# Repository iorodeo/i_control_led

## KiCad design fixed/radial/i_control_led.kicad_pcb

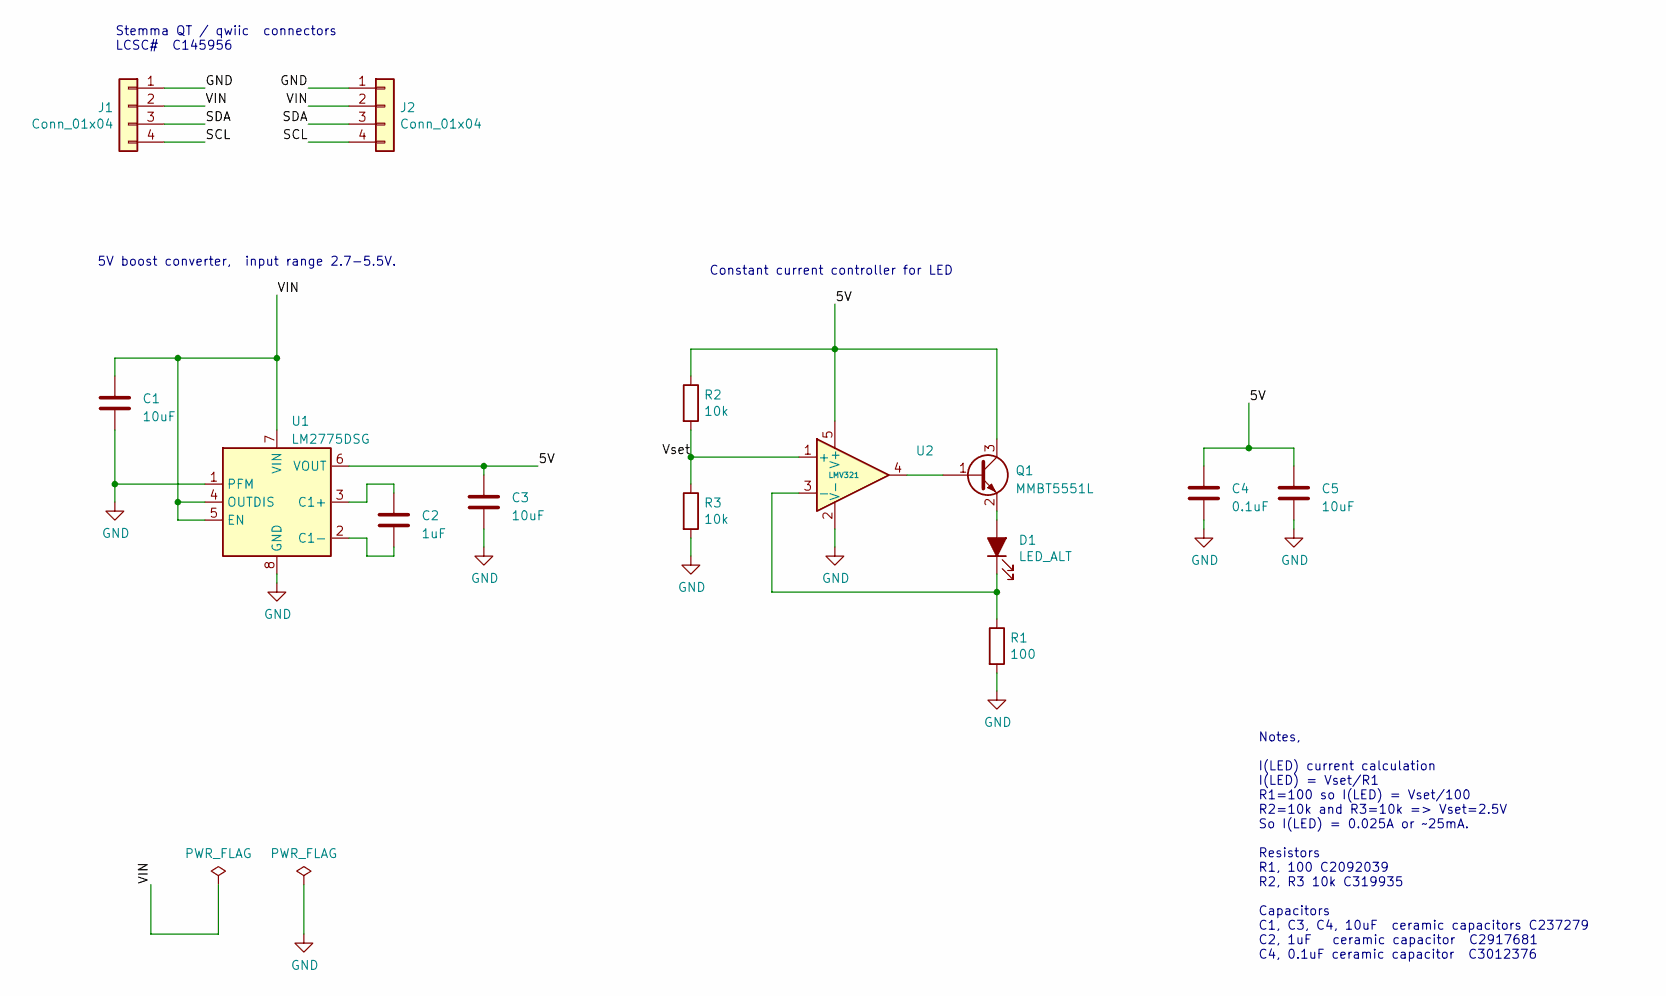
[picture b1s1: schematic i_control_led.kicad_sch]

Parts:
C1, C3, C5: 10uF; C_0402_1005Metric
C2: 1uF; C_0402_1005Metric
C4: 0.1uF; C_0402_1005Metric
D1: LED_ALT; LED_D3.0mm
J1, J2: Conn_01x04; BOOMELE_SMD_SH_4PIN_RT
Q1: MMBT5551L; SOT-23
R1: 100; R_0402_1005Metric
R2, R3: 10k; R_0402_1005Metric
U1: LM2775DSG; WSON-8-1EP_2x2mm_P0.5mm_EP0.9x1.6mm_ThermalVias
U2: LMV321; SOT-23-5

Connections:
/5V: C3.1, C4.1, C5.1, Q1.3 (C), R2.1, U1.6 (VOUT), U2.5 (V+)
/SCL: J1.4, J2.4
/SDA: J1.3, J2.3
/VIN: C1.2, J1.2, J2.2, U1.4 (OUTDIS), U1.5 (EN), U1.7 (VIN)
/Vset: R2.2, R3.1, U2.1 (+)
GND: C1.1, C3.2, C4.2, C5.2, J1.1, J2.1, R1.2, R3.2, U1.1 (PFM), U1.8 (GND), U1.9 (GND), U2.2 (V-)
unnamed: D1.2 (A), Q1.2 (E)
unnamed: D1.1 (K), R1.1, U2.3 (-)
unnamed: Q1.1 (B), U2.4
unnamed: C2.1, U1.3 (C1+)
unnamed: C2.2, U1.2 (C1-)

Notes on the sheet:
Stemma QT / qwiic connectors LCSC# C145956
Constant current controller for LED
Notes, I(LED) current calculation I(LED) = Vset/R1 R1=100 so I(LED) = Vset/100 R2=10k and R3=10k => Vset=2.5V So I(LED) = 0.025A or ~25mA. Resistors R1, 100 C2092039 R2, R3 10k C319935 Capacitors C1, C3, C4, 10uF ceramic capacitors C237279 C2, 1uF ceramic capacitor C2917681 C4, 0.1uF ceramic capaci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
5V boost converter, input range 2.7-5.5V.

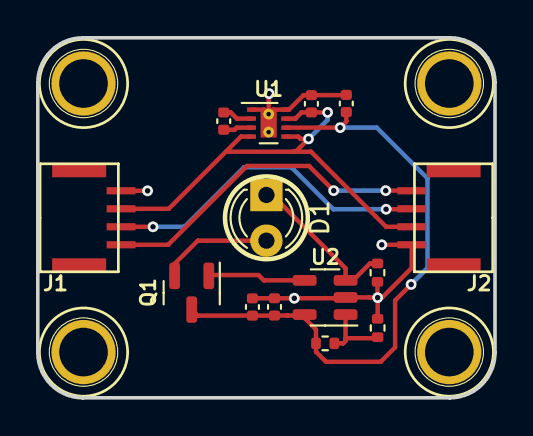
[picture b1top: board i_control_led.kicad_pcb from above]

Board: 2 copper layers, 25.4 x 20.0 mm, 18 parts (0 on the bottom side), 11 nets.

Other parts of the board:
M1, M2, M3, M4: MountingHole_2.5mm_Pad
